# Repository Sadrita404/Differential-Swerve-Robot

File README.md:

# Differential Swerve Robot

*This README was compiled with AI from my spoken notes.*

A four-module differential swerve robot with a turret, almost entirely 3D printed and driven by NEMA 17 steppers.

The mechanical parts cost about $110 to $150. A commercial FRC swerve module costs $500 or more with motors, and that is for one module. With breadboard electronics, the whole robot is under $200.

## Cost

| Build | Cost |
|---|---|
| Mechanical parts | $110 to $160 |
| Electronics, breadboard wiring | $57 to $66 |
| Total, breadboard build | $167 to $224 |

These are Amazon prices. The low end uses 38mm motors and 48 U-groove bearings. The high end uses 48mm motors, 64 bearings and better bolts. Filament, the optional turret bearing, the optional slip ring and the optional cover are not included. The full BOM is in `swerve_robot_bom.xlsx`.

## Printing

Printing everything takes a few days and a few rolls of filament.

The wheels are PLA. TPU should also work, and you can design your own wheel. Any wheel has to touch the ground in a line contact at the center of the wheel. If the contact point moves off center, the control code gets screwed up.

## Motors

The drive uses eight NEMA 17 steppers, two per module. I used 48mm motors, which have more torque than the robot needs. 38mm motors should also work. 23mm pancake NEMA 17s do not work because they are not strong enough.

## Stepper drivers

A4988, DRV8825 and TMC2209 stepsticks all work.

- **TMC2209** is the best of the three and is quiet. My PCB is laid out for A4988s, so TMC2209 UART control is not possible without big changes to the board. The drivers still run in step/dir mode.
- **A4988** is loud and buzzes, but you can play music with it. This is why my PCB was designed for A4988s.
- **DRV8825** shut off on their own in my experience. I don't recommend them.

## Electronics

You can wire the drivers on a breadboard or use a driver PCB. Breadboard wiring is harder but much cheaper.

My PCB is a 4-layer, 12-channel stepper driver board (PCBWay sponsored mine). I designed it as a general-purpose board for future projects, so it is bigger than this robot needs and the middle is empty. Only 9 channels are used here. There is room in the middle to add an MCU.

### Microcontroller

I used an ESP32. Any MCU with about 20 GPIO pins works.

- 16 pins for the 8 drive motors (step and dir each)
- 2 pins for the turret motor
- 1 pin for the global enable on the PCB, which saves a lot of power when the motors are idle

That is 19 pins. A second turret stepper adds 2 more, for 21.

### Battery

With TMC2209s and 48mm steppers, peak current draw is about 2A. A 6S 5Ah Li-ion pack is more than enough. These are safer than LiPos and on Amazon they usually come with a BMS and charger. They are more cube-shaped than a LiPo, which is lower profile.

The MCU can run from a USB power bank. If you want to run it from the main battery, add a 5V buck converter.

## Assembly tips

### U-groove bearing spacing

Each module uses 12 to 16 U-groove bearings, so the robot needs 48 to 64 in total. 8 bearings per module hold the ring gears. Another 4 to 8 per module mount the module in the chassis.

The most important dimension is the spacing of the U-groove bearings, both inside each module and in the wheel frame on the chassis.

- If the spacing is too small, the bearings don't hug the groove on the ring. The ring is too loose and the gears skip all the time.
- If the spacing is too big, there is too much friction. In the worst case you can't mount the ring at all.

The torus bead on the ring has a smaller radius than the groove in the bearing. As the robot breaks in, the bead wears to match the groove and the motion gets smoother.

If your spacing is off, use the included spacing jig to find the right value. The jig steps in 0.1mm increments. Then edit the STEP file to set that spacing and re-export the part.

### Gear skipping

If the modules skip under hard acceleration, fill more of the 8 mounting bearing slots around each module. More bearings hold the module tighter but also add friction.

## Turret

Turret assembly instructions are not included because the wiring depends on whether you use the PCB or a breadboard. The turret is fairly simple to put together. It lifts straight off, so you can reach the electronics underneath.

The turret uses one stepper by default. If you add a second turret stepper, you also need a slip ring so the wires can pass through the rotating joint. A 10-wire slip ring costs about $20, and the adapter plate and turret gear are designed to fit one.

The turret bearing can be 3D printed, and the file is included. You can also buy an equivalent bearing with a 100mm inner diameter and 125mm outer diameter for about $20. This is optional.

## Cover

The cover is optional and only cosmetic. SendCutSend quoted about $125 to laser cut it from polycarbonate (mine was sponsored). If you have access to a laser cutter, it costs only the material.

You can also 3D print the cover as four segments that lock together. The downside is that it hides the mechanism, which is the interesting part of the robot.

## Known limitations

- Steppers limit top speed and can lose position without encoders.
- The U-groove bearing ring mount has some play.
- The gears can skip at high speed.
- The design works best at low speed. A heavier-duty version would need large ring bearings and encoders.

## Credits

- James Lin reworked the V2 CAD around sideways 48mm motors and bevel gears.
- The Standard Manufacturing Company sponsored the robot. 
- LDO Motors sponsored the stepper motors.
- PCBWay sponsored the driver PCB.
- SendCutSent sponsored the transparent cover.

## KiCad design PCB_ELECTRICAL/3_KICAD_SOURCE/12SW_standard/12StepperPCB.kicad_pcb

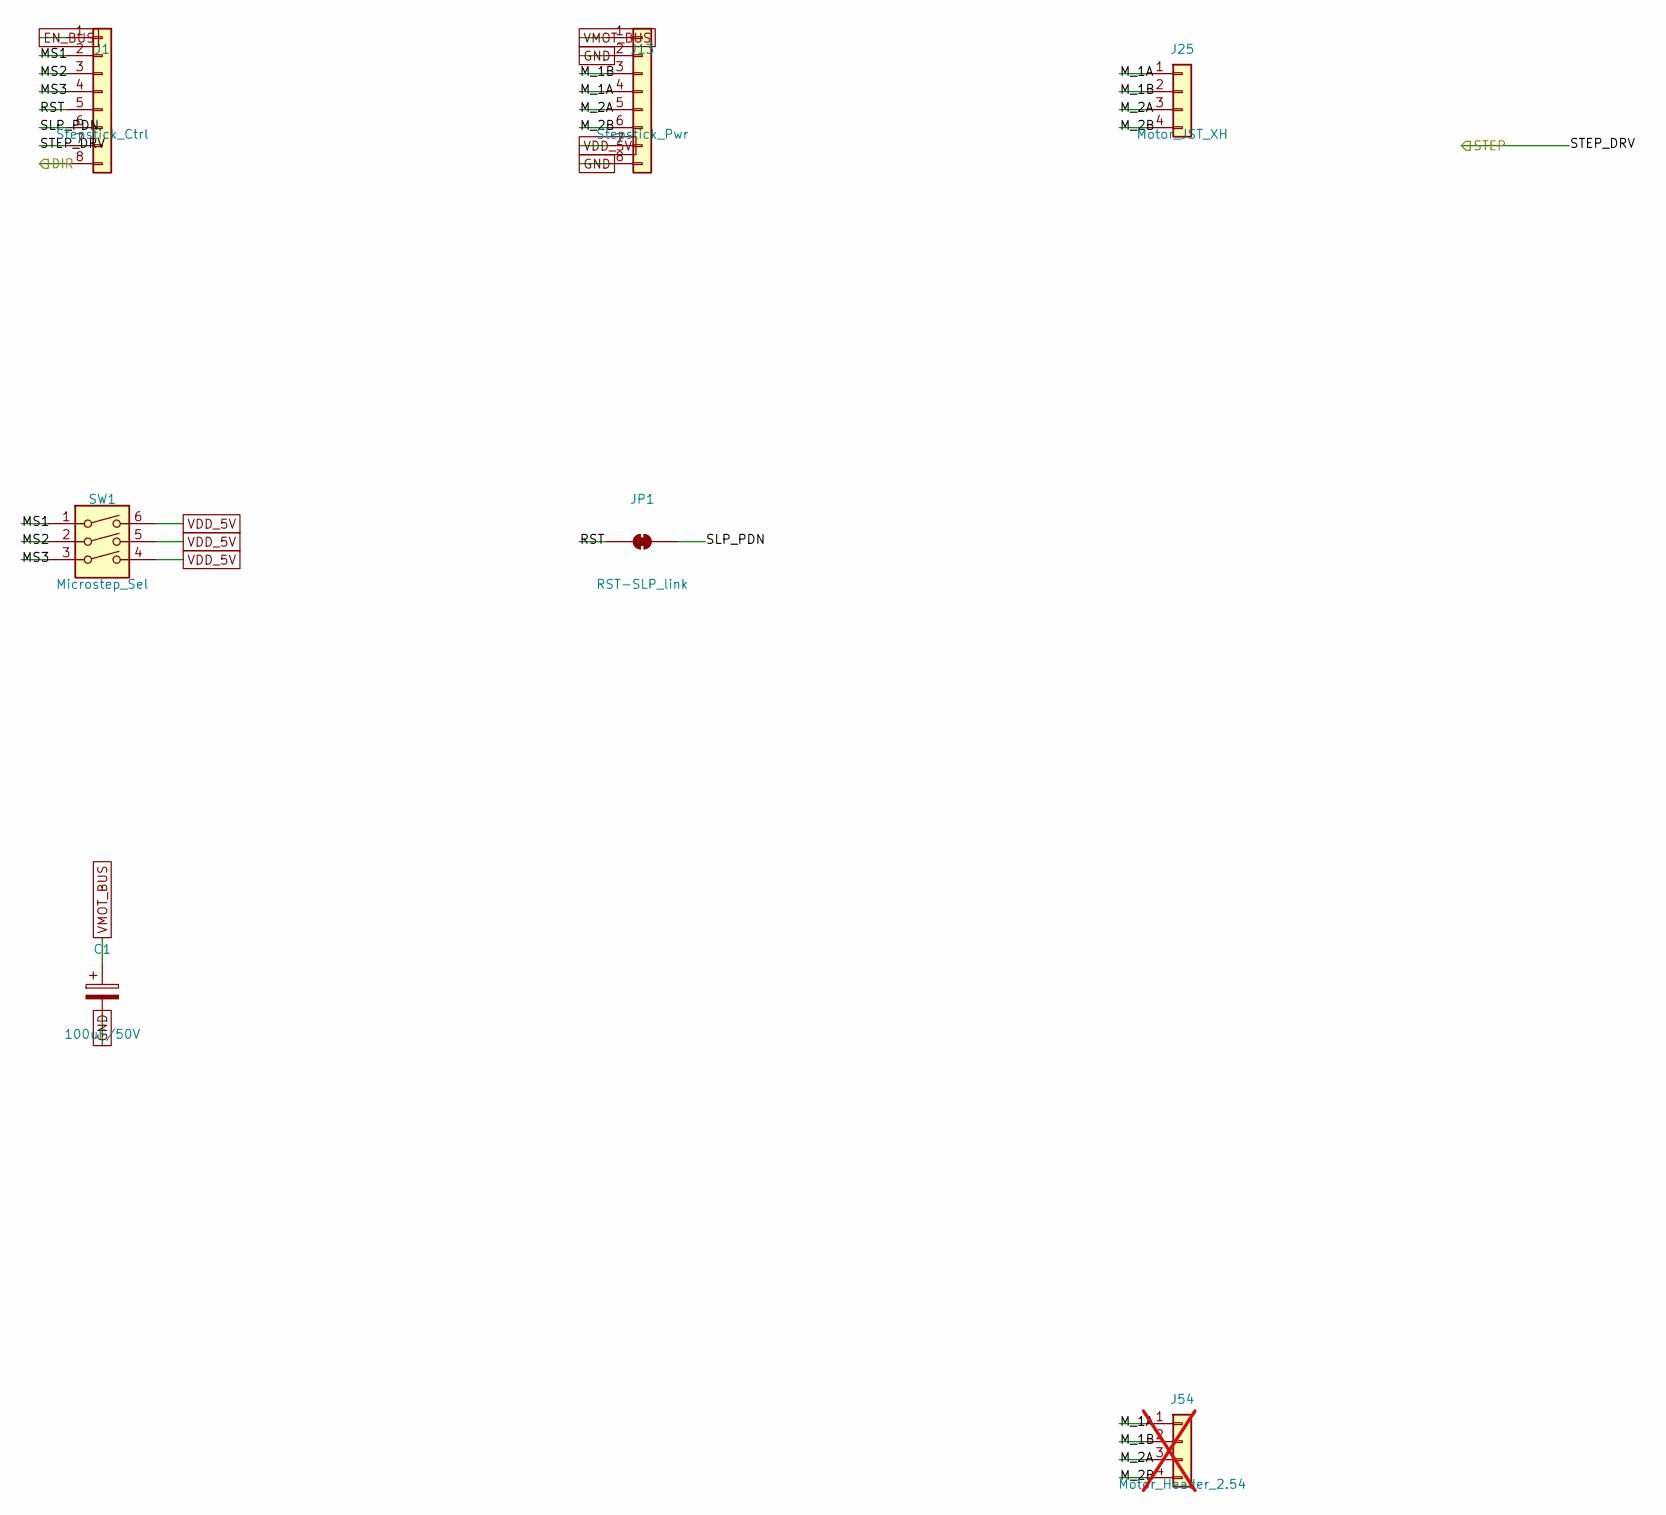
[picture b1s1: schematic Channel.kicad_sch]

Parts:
C1: 100uF/50V; CP_Radial_D8.0mm_P3.50mm; MPN EEU-FR1H101
J1: Stepstick_Ctrl; PinSocket_1x08_P2.54mm_Vertical; MPN PPTC081LFBN-RC
J13: Stepstick_Pwr; PinSocket_1x08_P2.54mm_Vertical; MPN PPTC081LFBN-RC
J25: Motor_JST_XH; JST_XH_B4B-XH-A_1x04_P2.50mm_Vertical; MPN B4B-XH-A(LF)(SN)
J54: Motor_Header_2.54; PinHeader_1x04_P2.54mm_Vertical; MPN PREC004SAAN-RC; not fitted
JP1: RST-SLP_link; SolderJumper-2_P1.3mm_Bridged_RoundedPad1.0x1.5mm
SW1: Microstep_Sel; SW_DIP_SPSTx03_Slide_9.78x9.8mm_W7.62mm_P2.54mm; MPN 206-3

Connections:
/Channel1/MS1: J1.2, SW1.1
/Channel1/MS2: J1.3, SW1.2
/Channel1/MS3: J1.4, SW1.3
/Channel1/M_1A: J13.4, J25.1, J54.1
/Channel1/M_1B: J13.3, J25.2, J54.2
/Channel1/M_2A: J13.5, J25.3, J54.3
/Channel1/M_2B: J13.6, J25.4, J54.4
/Channel1/RST: J1.5, JP1.1 (A)
/Channel1/SLP_PDN: J1.6, JP1.2 (B)
DIR1: J1.8; also elsewhere on the board
EN_BUS: J1.1; also elsewhere on the board
GND: C1.2, J13.2, J13.8; also elsewhere on the board
STEP1: J1.7; also elsewhere on the board
VDD_5V: J13.7, SW1.4, SW1.5, SW1.6; also elsewhere on the board
VMOT_BUS: C1.1, J13.1; also elsewhere on the board

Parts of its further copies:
C4, C7, C10, C13, C16, C19, C22, C25, C28, C31, C34: 100uF/50V; CP_Radial_D8.0mm_P3.50mm; MPN EEU-FR1H101
J2, J3, J4, J5, J6, J7, J8, J9, J10, J11, J12: Stepstick_Ctrl; PinSocket_1x08_P2.54mm_Vertical; MPN PPTC081LFBN-RC
J14, J15, J16, J17, J18, J19, J20, J21, J22, J23, J24: Stepstick_Pwr; PinSocket_1x08_P2.54mm_Vertical; MPN PPTC081LFBN-RC
J26, J27, J28, J29, J30, J31, J32, J33, J34, J35, J36: Motor_JST_XH; JST_XH_B4B-XH-A_1x04_P2.50mm_Vertical; MPN B4B-XH-A(LF)(SN)
J55, J56, J57, J58, J59, J60, J61, J62, J63, J64, J65: Motor_Header_2.54; PinHeader_1x04_P2.54mm_Vertical; MPN PREC004SAAN-RC; not fitted
JP2, JP3, JP4, JP5, JP6, JP7, JP8, JP9, JP10, JP11, JP12: RST-SLP_link; SolderJumper-2_P1.3mm_Bridged_RoundedPad1.0x1.5mm
SW2, SW3, SW4, SW5, SW6, SW7, SW8, SW9, SW10, SW11, SW12: Microstep_Sel; SW_DIP_SPSTx03_Slide_9.78x9.8mm_W7.62mm_P2.54mm; MPN 206-3

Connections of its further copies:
/Channel2/MS1: J2.2, SW2.1
/Channel2/MS2: J2.3, SW2.2
/Channel2/MS3: J2.4, SW2.3
/Channel2/M_1A: J14.4, J26.1, J55.1
/Channel2/M_1B: J14.3, J26.2, J55.2
/Channel2/M_2A: J14.5, J26.3, J55.3
/Channel2/M_2B: J14.6, J26.4, J55.4
/Channel2/RST: J2.5, JP2.1 (A)
/Channel2/SLP_PDN: J2.6, JP2.2 (B)
/Channel3/MS1: J3.2, SW3.1
/Channel3/MS2: J3.3, SW3.2
/Channel3/MS3: J3.4, SW3.3
/Channel3/M_1A: J15.4, J27.1, J56.1
/Channel3/M_1B: J15.3, J27.2, J56.2
/Channel3/M_2A: J15.5, J27.3, J56.3
/Channel3/M_2B: J15.6, J27.4, J56.4
/Channel3/RST: J3.5, JP3.1 (A)
/Channel3/SLP_PDN: J3.6, JP3.2 (B)
/Channel4/MS1: J4.2, SW4.1
/Channel4/MS2: J4.3, SW4.2
/Channel4/MS3: J4.4, SW4.3
/Channel4/M_1A: J16.4, J28.1, J57.1
/Channel4/M_1B: J16.3, J28.2, J57.2
/Channel4/M_2A: J16.5, J28.3, J57.3
/Channel4/M_2B: J16.6, J28.4, J57.4
/Channel4/RST: J4.5, JP4.1 (A)
/Channel4/SLP_PDN: J4.6, JP4.2 (B)
/Channel5/MS1: J5.2, SW5.1
/Channel5/MS2: J5.3, SW5.2
/Channel5/MS3: J5.4, SW5.3
/Channel5/M_1A: J17.4, J29.1, J58.1
/Channel5/M_1B: J17.3, J29.2, J58.2
/Channel5/M_2A: J17.5, J29.3, J58.3
/Channel5/M_2B: J17.6, J29.4, J58.4
/Channel5/RST: J5.5, JP5.1 (A)
/Channel5/SLP_PDN: J5.6, JP5.2 (B)
/Channel6/MS1: J6.2, SW6.1
/Channel6/MS2: J6.3, SW6.2
/Channel6/MS3: J6.4, SW6.3
/Channel6/M_1A: J18.4, J30.1, J59.1
/Channel6/M_1B: J18.3, J30.2, J59.2
/Channel6/M_2A: J18.5, J30.3, J59.3
/Channel6/M_2B: J18.6, J30.4, J59.4
/Channel6/RST: J6.5, JP6.1 (A)
/Channel6/SLP_PDN: J6.6, JP6.2 (B)
/Channel7/MS1: J7.2, SW7.1
/Channel7/MS2: J7.3, SW7.2
/Channel7/MS3: J7.4, SW7.3
/Channel7/M_1A: J19.4, J31.1, J60.1
/Channel7/M_1B: J19.3, J31.2, J60.2
/Channel7/M_2A: J19.5, J31.3, J60.3
/Channel7/M_2B: J19.6, J31.4, J60.4
/Channel7/RST: J7.5, JP7.1 (A)
/Channel7/SLP_PDN: J7.6, JP7.2 (B)
/Channel8/MS1: J8.2, SW8.1
/Channel8/MS2: J8.3, SW8.2
/Channel8/MS3: J8.4, SW8.3
/Channel8/M_1A: J20.4, J32.1, J61.1
/Channel8/M_1B: J20.3, J32.2, J61.2
/Channel8/M_2A: J20.5, J32.3, J61.3
/Channel8/M_2B: J20.6, J32.4, J61.4
/Channel8/RST: J8.5, JP8.1 (A)
/Channel8/SLP_PDN: J8.6, JP8.2 (B)
/Channel9/MS1: J9.2, SW9.1
/Channel9/MS2: J9.3, SW9.2
/Channel9/MS3: J9.4, SW9.3
/Channel9/M_1A: J21.4, J33.1, J62.1
/Channel9/M_1B: J21.3, J33.2, J62.2
/Channel9/M_2A: J21.5, J33.3, J62.3
/Channel9/M_2B: J21.6, J33.4, J62.4
/Channel9/RST: J9.5, JP9.1 (A)
/Channel9/SLP_PDN: J9.6, JP9.2 (B)
/Channel10/MS1: J10.2, SW10.1
/Channel10/MS2: J10.3, SW10.2
/Channel10/MS3: J10.4, SW10.3
/Channel10/M_1A: J22.4, J34.1, J63.1
/Channel10/M_1B: J22.3, J34.2, J63.2
/Channel10/M_2A: J22.5, J34.3, J63.3
/Channel10/M_2B: J22.6, J34.4, J63.4
/Channel10/RST: J10.5, JP10.1 (A)
/Channel10/SLP_PDN: J10.6, JP10.2 (B)
/Channel11/MS1: J11.2, SW11.1
/Channel11/MS2: J11.3, SW11.2
/Channel11/MS3: J11.4, SW11.3
/Channel11/M_1A: J23.4, J35.1, J64.1
/Channel11/M_1B: J23.3, J35.2, J64.2
/Channel11/M_2A: J23.5, J35.3, J64.3
/Channel11/M_2B: J23.6, J35.4, J64.4
/Channel11/RST: J11.5, JP11.1 (A)
/Channel11/SLP_PDN: J11.6, JP11.2 (B)
/Channel12/MS1: J12.2, SW12.1
/Channel12/MS2: J12.3, SW12.2
/Channel12/MS3: J12.4, SW12.3
/Channel12/M_1A: J24.4, J36.1, J65.1
/Channel12/M_1B: J24.3, J36.2, J65.2
/Channel12/M_2A: J24.5, J36.3, J65.3
/Channel12/M_2B: J24.6, J36.4, J65.4
/Channel12/RST: J12.5, JP12.1 (A)
/Channel12/SLP_PDN: J12.6, JP12.2 (B)
DIR2: J2.8; also elsewhere on the board
DIR3: J3.8; also elsewhere on the board
DIR4: J4.8; also elsewhere on the board
DIR5: J5.8; also elsewhere on the board
DIR6: J6.8; also elsewhere on the board
DIR7: J7.8; also elsewhere on the board
DIR8: J8.8; also elsewhere on the board
DIR9: J9.8; also elsewhere on the board
DIR10: J10.8; also elsewhere on the board
DIR11: J11.8; also elsewhere on the board
DIR12: J12.8; also elsewhere on the board
EN_BUS: J2.1, J3.1, J4.1, J5.1, J6.1, J7.1, J8.1, J9.1, J10.1, J11.1, J12.1; also elsewhere on the board
GND: C4.2, C7.2, C10.2, C13.2, C16.2, C19.2, C22.2, C25.2, C28.2, C31.2, C34.2, J14.2, J14.8, J15.2, J15.8, J16.2, J16.8, J17.2, J17.8, J18.2, J18.8, J19.2, J19.8, J20.2, J20.8, J21.2, J21.8, J22.2, J22.8, J23.2, J23.8, J24.2, J24.8; also elsewhere on the board
STEP2: J2.7; also elsewhere on the board
STEP3: J3.7; also elsewhere on the board
STEP4: J4.7; also elsewhere on the board
STEP5: J5.7; also elsewhere on the board
STEP6: J6.7; also elsewhere on the board
STEP7: J7.7; also elsewhere on the board
STEP8: J8.7; also elsewhere on the board
STEP9: J9.7; also elsewhere on the board
STEP10: J10.7; also elsewhere on the board
STEP11: J11.7; also elsewhere on the board
STEP12: J12.7; also elsewhere on the board
VDD_5V: J14.7, J15.7, J16.7, J17.7, J18.7, J19.7, J20.7, J21.7, J22.7, J23.7, J24.7, SW2.4, SW2.5, SW2.6, SW3.4, SW3.5, SW3.6, SW4.4, SW4.5, SW4.6, SW5.4, SW5.5, SW5.6, SW6.4, SW6.5, SW6.6, SW7.4, SW7.5, SW7.6, SW8.4, SW8.5, SW8.6, SW9.4, SW9.5, SW9.6, SW10.4, SW10.5, SW10.6, SW11.4, SW11.5, SW11.6, SW12.4, SW12.5, SW12.6; also elsewhere on the board
VMOT_BUS: C4.1, C7.1, C10.1, C13.1, C16.1, C19.1, C22.1, C25.1, C28.1, C31.1, C34.1, J14.1, J15.1, J16.1, J17.1, J18.1, J19.1, J20.1, J21.1, J22.1, J23.1, J24.1; also elsewhere on the board

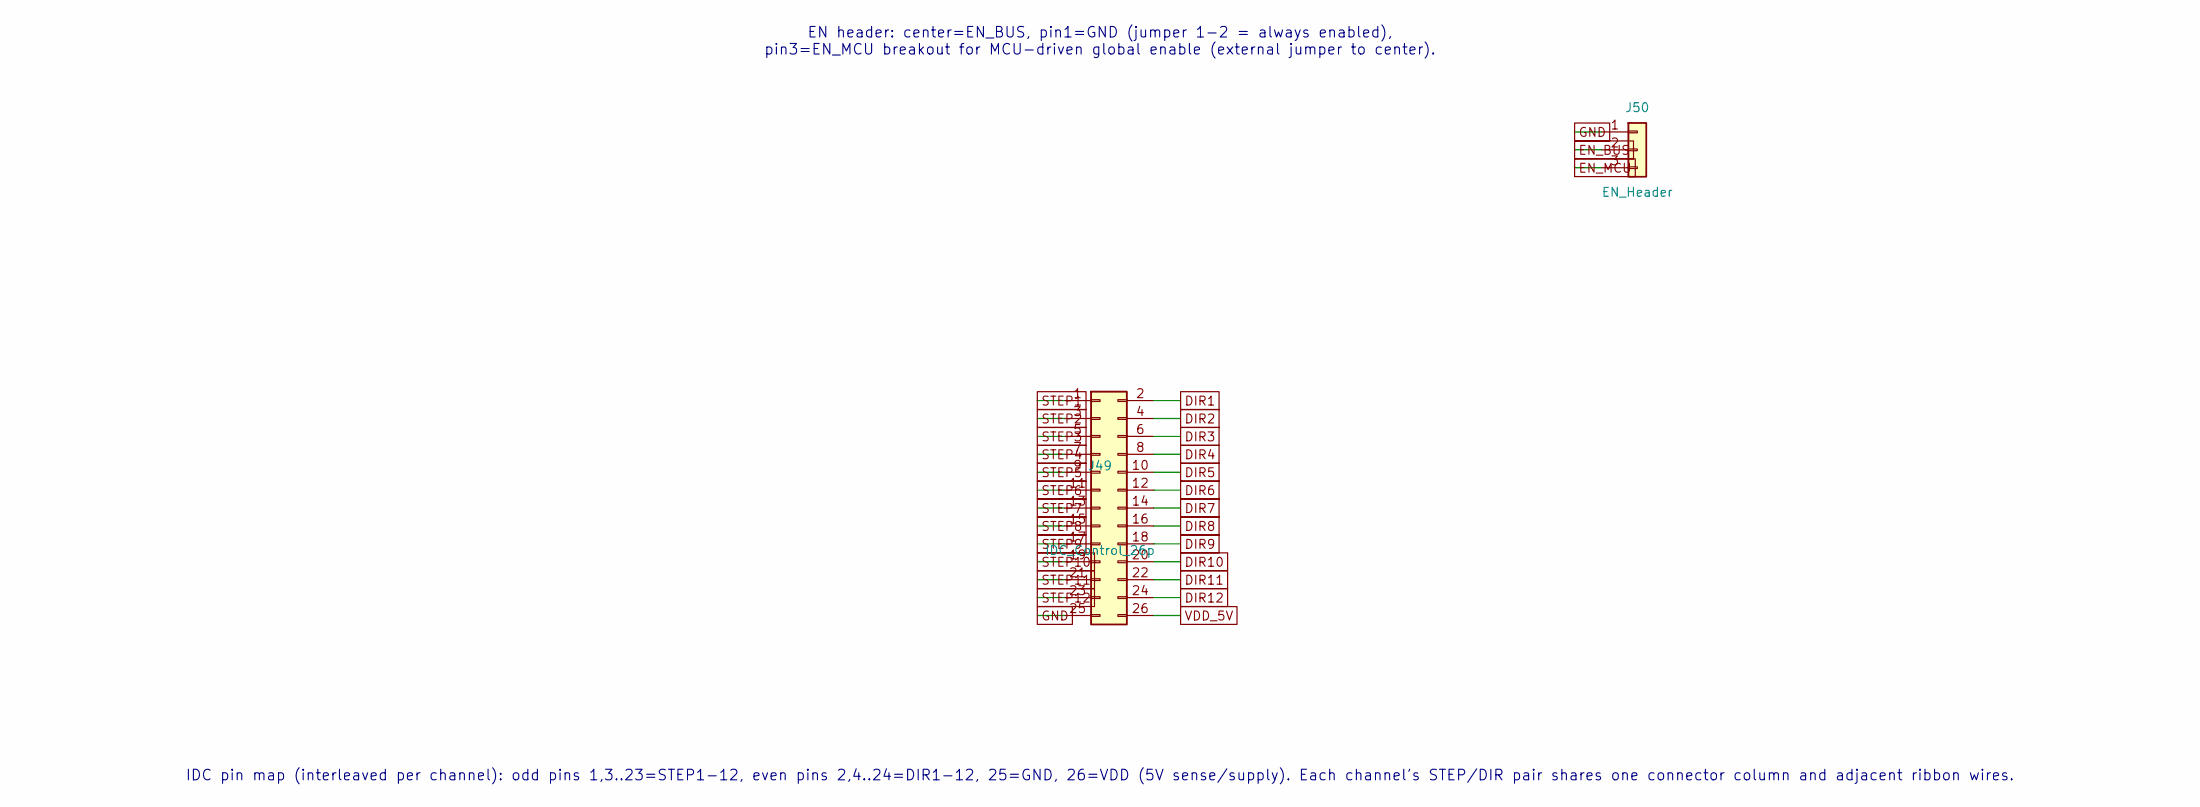
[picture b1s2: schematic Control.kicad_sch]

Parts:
J49: IDC_Control_26p; IDC-Header_2x13_P2.54mm_Vertical; MPN 302-S261
J50: EN_Header; PinHeader_1x03_P2.54mm_Vertical; MPN PREC003SAAN-RC

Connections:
DIR1: J49.2; also elsewhere on the board
DIR2: J49.4; also elsewhere on the board
DIR3: J49.6; also elsewhere on the board
DIR4: J49.8; also elsewhere on the board
DIR5: J49.10; also elsewhere on the board
DIR6: J49.12; also elsewhere on the board
DIR7: J49.14; also elsewhere on the board
DIR8: J49.16; also elsewhere on the board
DIR9: J49.18; also elsewhere on the board
DIR10: J49.20; also elsewhere on the board
DIR11: J49.22; also elsewhere on the board
DIR12: J49.24; also elsewhere on the board
EN_BUS: J50.2; also elsewhere on the board
EN_MCU: J50.3
GND: J49.25, J50.1; also elsewhere on the board
STEP1: J49.1; also elsewhere on the board
STEP2: J49.3; also elsewhere on the board
STEP3: J49.5; also elsewhere on the board
STEP4: J49.7; also elsewhere on the board
STEP5: J49.9; also elsewhere on the board
STEP6: J49.11; also elsewhere on the board
STEP7: J49.13; also elsewhere on the board
STEP8: J49.15; also elsewhere on the board
STEP9: J49.17; also elsewhere on the board
STEP10: J49.19; also elsewhere on the board
STEP11: J49.21; also elsewhere on the board
STEP12: J49.23; also elsewhere on the board
VDD_5V: J49.26; also elsewhere on the board

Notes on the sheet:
EN header: center=EN_BUS, pin1=GND (jumper 1-2 = always enabled), pin3=EN_MCU breakout for MCU-driven global enable (external jumper to center).
IDC pin map (interleaved per channel): odd pins 1,3..23=STEP1-12, even pins 2,4..24=DIR1-12, 25=GND, 26=VDD (5V sense/supply). Each channel's STEP/DIR pair shares one connector column and adjacent ribbon wires.

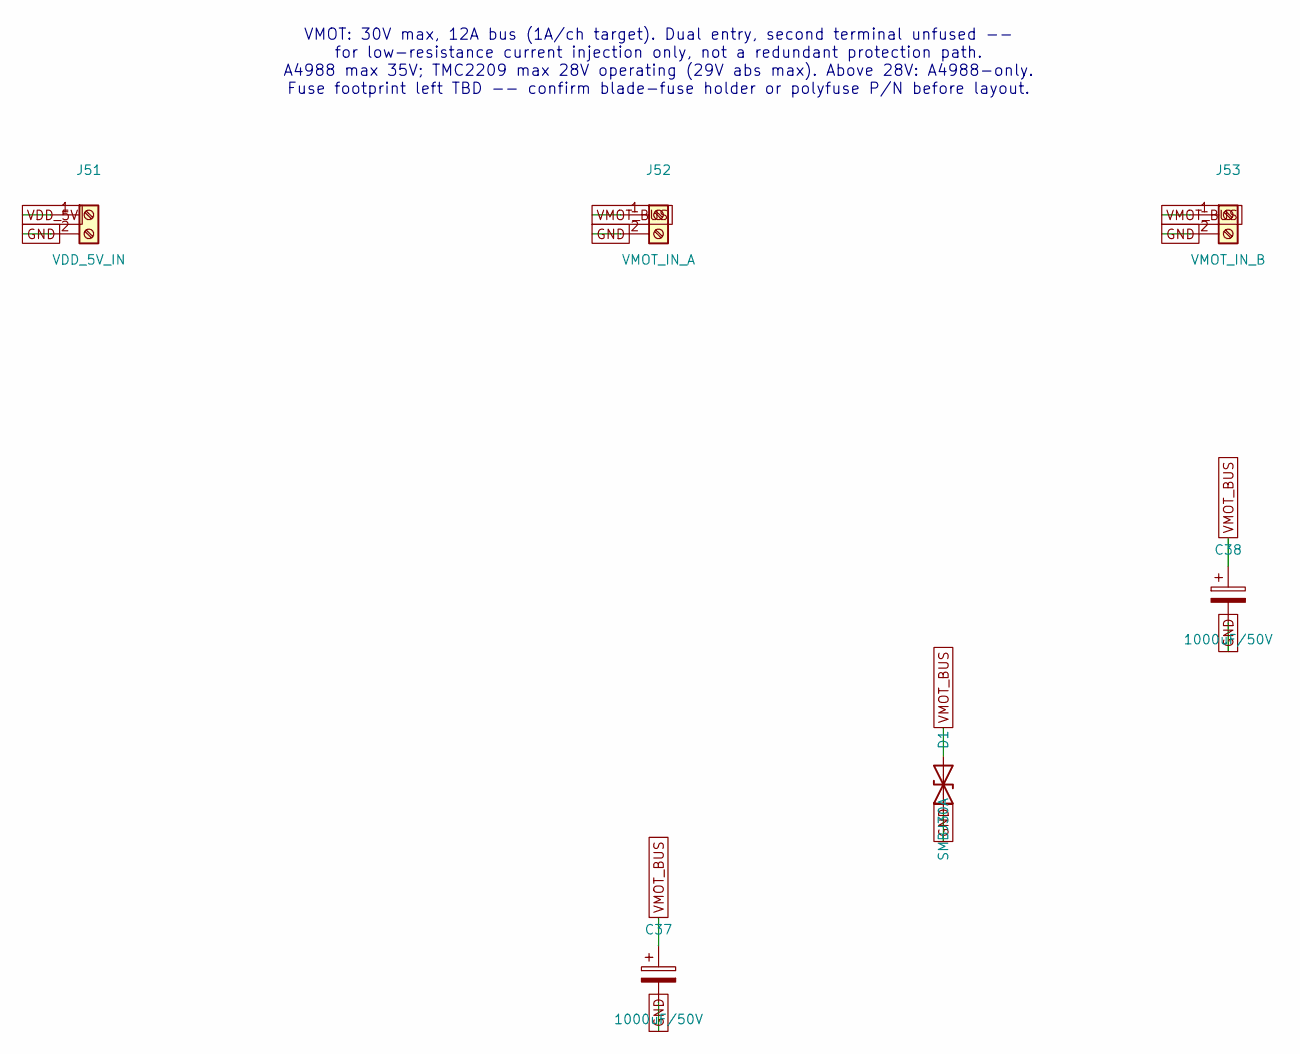
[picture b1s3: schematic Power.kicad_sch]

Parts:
C37, C38: 1000uF/50V; CP_Radial_D12.5mm_P5.00mm; MPN EEU-FR1H102
D1: SMBJ30A; D_SMB; MPN SMBJ30A
J51: VDD_5V_IN; TerminalBlock_Phoenix_MKDS-1,5-2-5.08_1x02_P5.08mm_Horizont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; MPN 1715721
J52: VMOT_IN_A; TerminalBlock_Phoenix_MKDS-3-2-5.08_1x02_P5.08mm_Horizontal; MPN 1711725
J53: VMOT_IN_B; TerminalBlock_Phoenix_MKDS-3-2-5.08_1x02_P5.08mm_Horizontal; MPN 1711725

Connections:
GND: C37.2, C38.2, D1.1 (A1), J51.2, J52.2, J53.2; also elsewhere on the board
VDD_5V: J51.1; also elsewhere on the board
VMOT_BUS: C37.1, C38.1, D1.2 (A2), J52.1, J53.1; also elsewhere on the board

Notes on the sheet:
VMOT: 30V max, 12A bus (1A/ch target). Dual entry, second terminal unfused -- for low-resistance current injection only, not a redundant protection path. A4988 max 35V; TMC2209 max 28V operating (29V abs max). Above 28V: A4988-only. Fuse footprint left TBD -- confirm blade-fuse holder or polyfuse P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

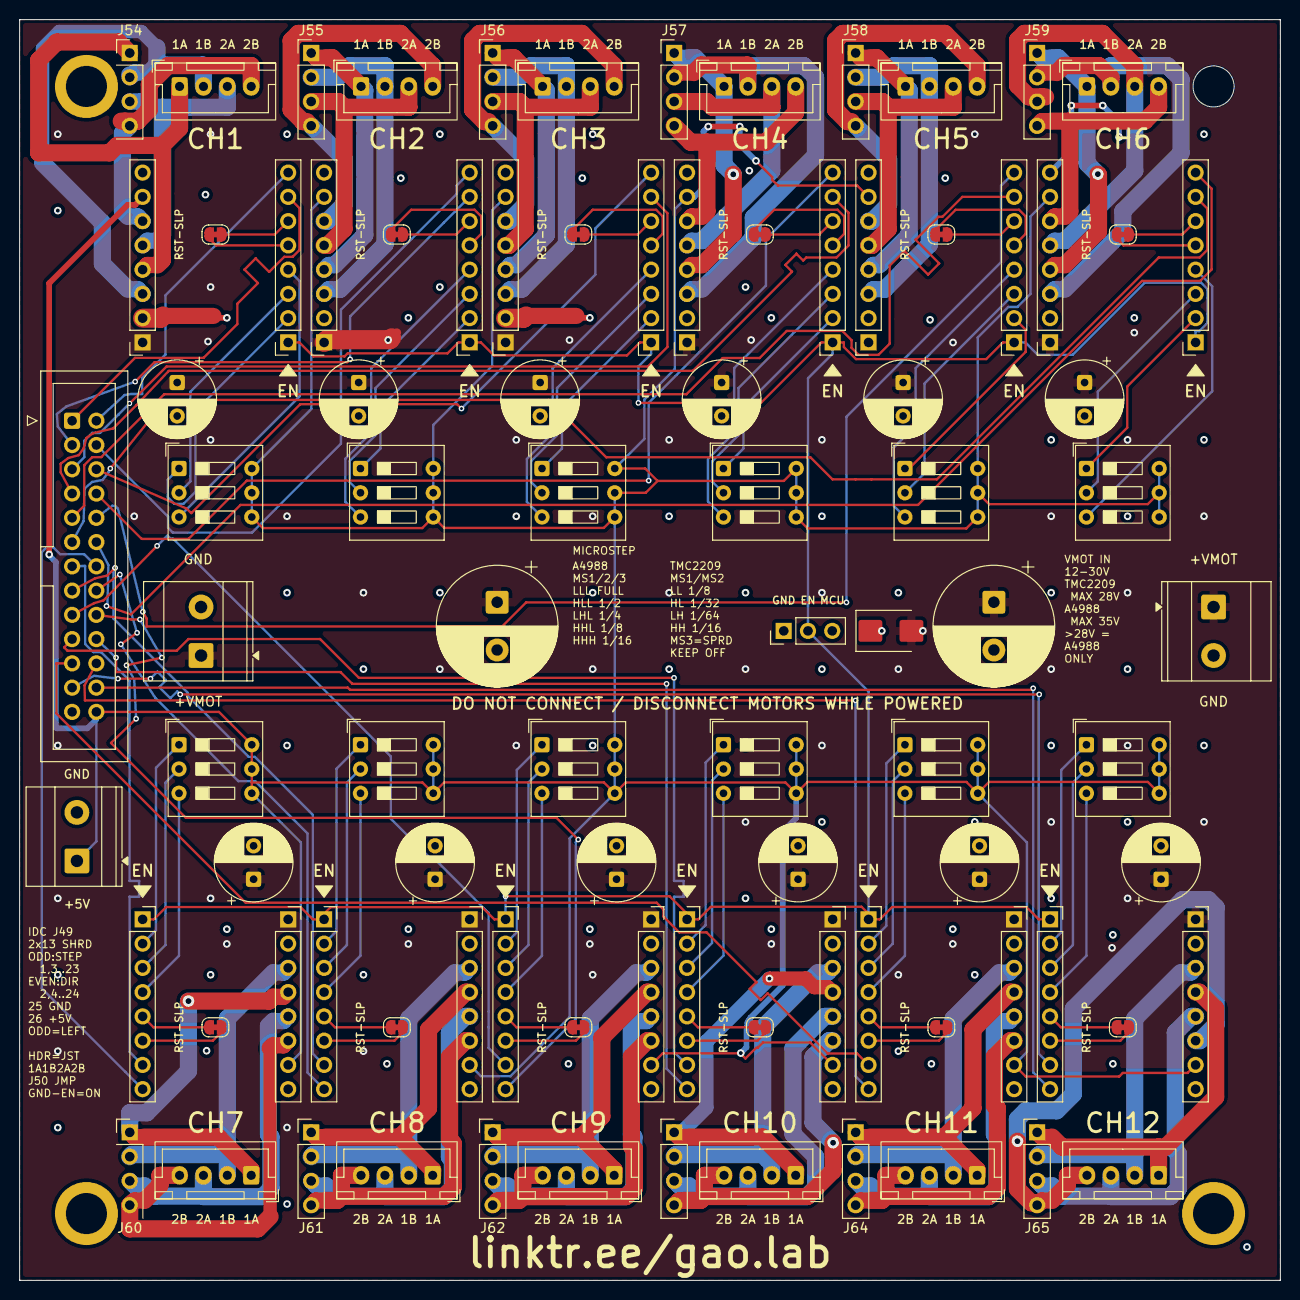
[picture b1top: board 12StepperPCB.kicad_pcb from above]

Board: 4 copper layers, 132.0 x 132.0 mm, 96 parts (0 on the bottom side), 136 nets.

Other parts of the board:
H1, H2, H3, H4: MountingHole_3.2mm_M3_Pad

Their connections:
GND: H1.1, H3.1, H4.1; also elsewhere on the board
